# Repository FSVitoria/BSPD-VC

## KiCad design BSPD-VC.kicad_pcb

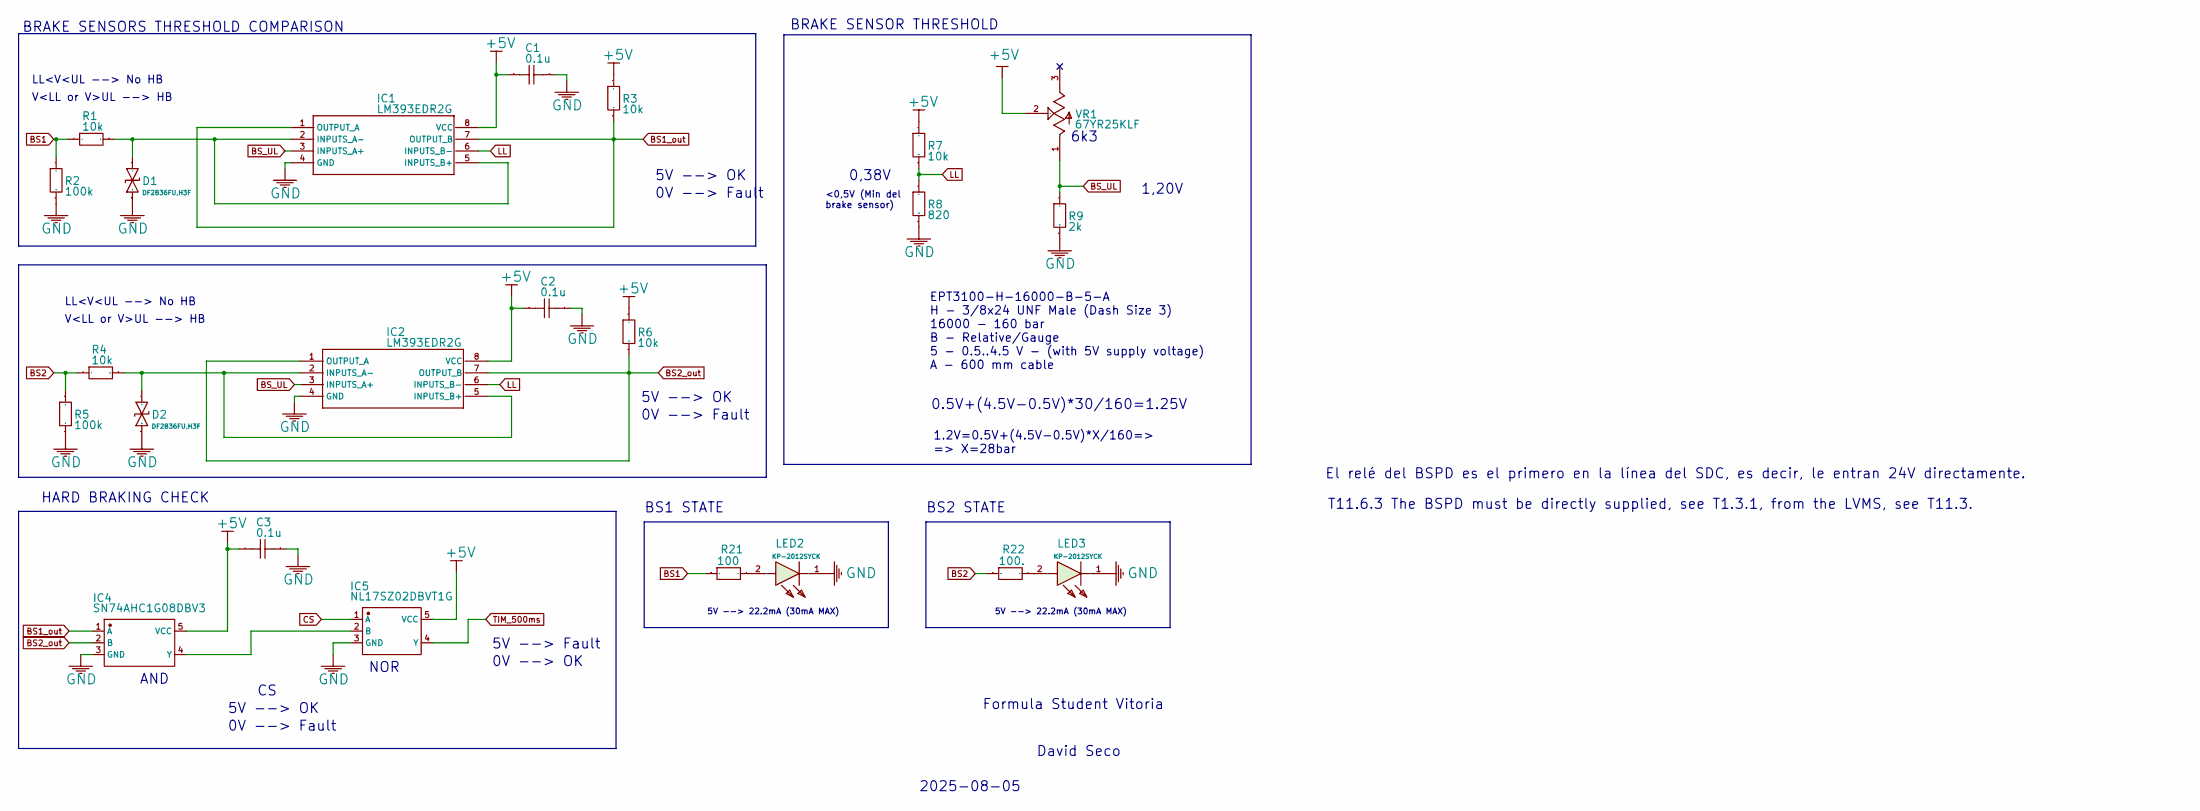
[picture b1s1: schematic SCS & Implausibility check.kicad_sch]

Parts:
C1, C2, C3: 0.1u; C0805
D1, D2: DF2B36FU,H3F; SOD-323_L1.7-W1.3-LS2.5-BI; Manufacturer Part DF2B36FU,H3F
IC1, IC2: LM393EDR2G; SOIC127P600X175-8N
IC4: SN74AHC1G08DBV3; SOT-23-5_L2.9-W1.6-P0.95-LS2.8-BR; Manufacturer Part SN74AHC1G08DBV3
IC5: NL17SZ02DBVT1G; SC-74A-5_L2.9-W1.6-P0.95-LS2.8-BR; Manufacturer Part NL17SZ02DBVT1G
LED2, LED3: KP-2012SYCK; LED_APHCM2012SURCK-F01
R1, R3, R4, R6, R7: 10k; R0805_NEW
R2, R5: 100k; R0805_NEW
R8: 820; R0805_NEW
R9: 2k; R0805_NEW
R21: 100; R0805
R22: 100.; R0805
VR1: 67YR25KLF; TRIM_67YR25KLFTB

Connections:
+5V: C1.1, C2.1, C3.2, IC1.8 (VCC), IC2.8 (VCC), IC4.5 (VCC), IC5.5 (VCC), R3.2, R6.2, R7.2, VR1.2; also elsewhere on the board
BS1: R1.2, R2.2, R21.1; also elsewhere on the board
BS1_out: IC1.1 (OUTPUT_A), IC1.7 (OUTPUT_B), IC4.1 (A), R3.1
BS2: R4.2, R5.2, R22.1; also elsewhere on the board
BS2_out: IC2.1 (OUTPUT_A), IC2.7 (OUTPUT_B), IC4.2 (B), R6.1
BS_UL: IC1.3 (INPUTS_A+), IC2.3 (INPUTS_A+), R9.2, VR1.1
CS: IC5.1 (A); also elsewhere on the board
GND: C1.2, C2.2, C3.1, D1.1, D2.1, IC1.4 (GND), IC2.4 (GND), IC4.3 (GND), IC5.3 (GND), LED2.1 (K), LED3.1 (K), R2.1, R5.1, R8.1, R9.1; also elsewhere on the board
LL: IC1.6 (INPUTS_B-), IC2.6 (INPUTS_B-), R7.1, R8.2
unnamed: D1.2, IC1.2 (INPUTS_A-), IC1.5 (INPUTS_B+), R1.1
unnamed: D2.2, IC2.2 (INPUTS_A-), IC2.5 (INPUTS_B+), R4.1
unnamed: IC4.4 (Y), IC5.2 (B)
unnamed: LED2.2 (A), R21.2
unnamed: LED3.2 (A), R22.2
TIM_500ms: IC5.4 (Y); also elsewhere on the board

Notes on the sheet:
5V --> 22.2mA (30mA MAX)
0,38V
El relé del BSPD es el primero en la línea del SDC, es decir, le entran 24V directamente.
5V --> OK
1.2V=0.5V+(4.5V-0.5V)*X/160=> => X=28bar
LL<V<UL --> No HB
6k3
NOR
5V --> Fault
BS2 STATE
V<LL or V>UL --> HB
0V --> Fault
T11.6.3 The BSPD must be directly supplied, see T1.3.1, from the LVMS, see T11.3.
BS1 STATE
0V --> OK
0.5V+(4.5V-0.5V)*30/160=1.25V
EPT3100-H-16000-B-5-A H - 3/8x24 UNF Male (Dash Size 3) 16000 - 160 bar B - Relative/Gauge 5 - 0.5..4.5 V - (with 5V supply voltage) A - 600 mm cable
Formula Student Vitoria
David Seco
AND
<0,5V (Min del brake sensor)
BRAKE SENSOR THRESHOLD
2025-08-05
5V --> 22.2mA (30mA MAX)
1,20V
BRAKE SENSORS THRESHOLD COMPARISON
HARD BRAKING CHECK

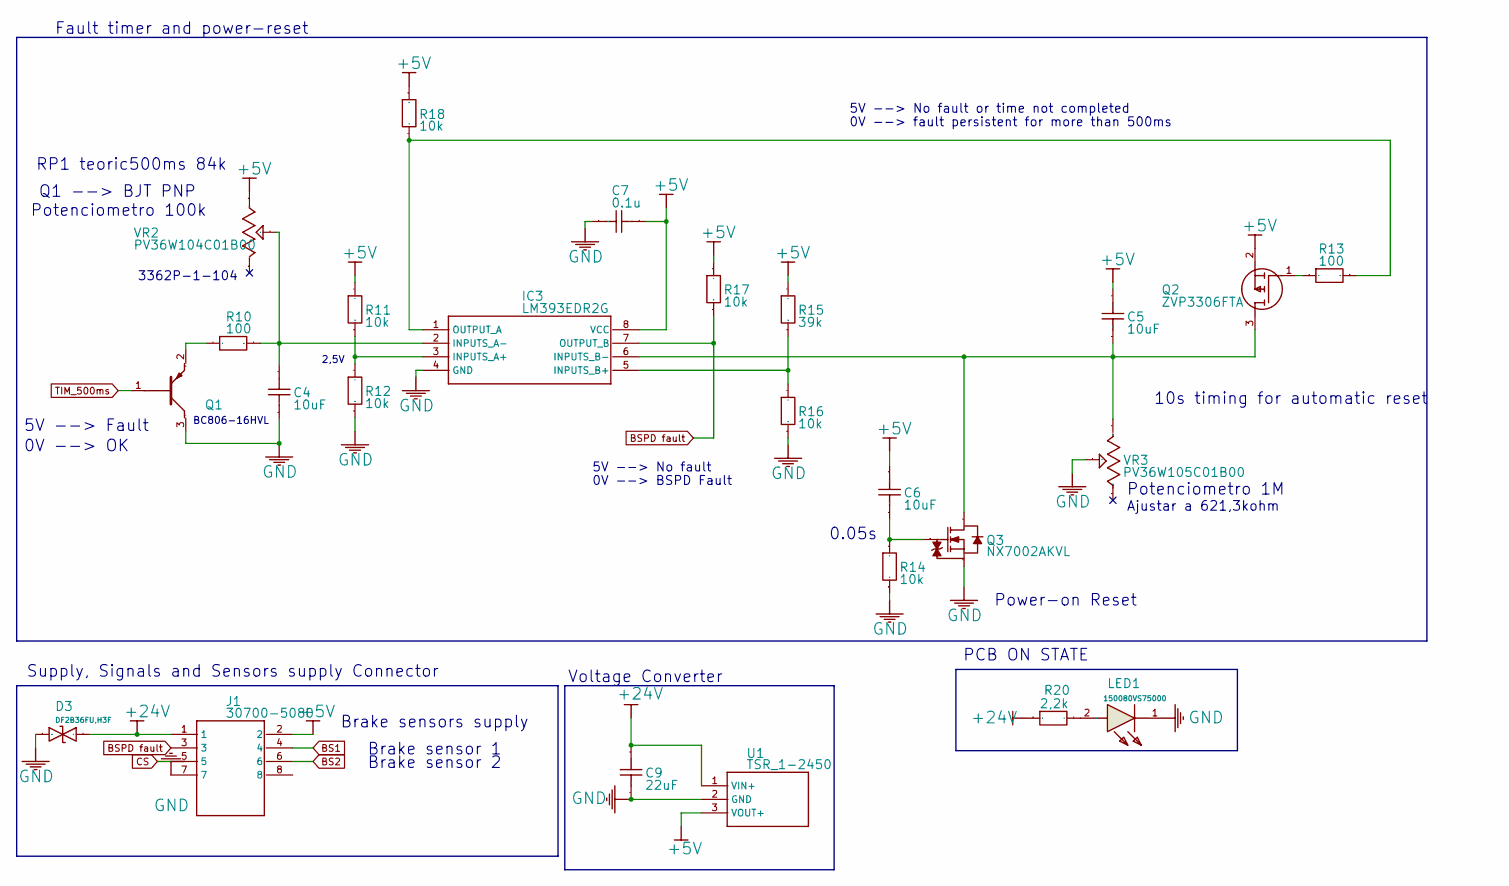
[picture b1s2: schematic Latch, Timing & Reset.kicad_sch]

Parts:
C4, C5, C6: 10uF; CAPAE430X610N
C7: 0.1u; C0805
C9: 22uF; C0805
D3: DF2B36FU,H3F; SOD-323_L1.7-W1.3-LS2.5-BI; Manufacturer Part DF2B36FU,H3F
IC3: LM393EDR2G; SOIC127P600X175-8N
J1: 30700-5080; 307005080
LED1: 150080VS75000; LEDC2012X80N
Q1: BC806-16HVL; SOT95P230X110-3N
Q2: ZVP3306FTA; SOT96P240X100-3N
Q3: NX7002AKVL; TO-236AB_L2.9-W1.3-P0.95-LS2.3-BR; Manufacturer Part NX7002AKVL
R10, R13: 100; R0805_NEW
R11, R12, R14, R16, R17, R18: 10k; R0805_NEW
R15: 39k; R0805_NEW
R20: 2,2k; R0805
U1: TSR_1-2450; TSR-1-24120
VR2: PV36W104C01B00; TRIM_PV36W104C01B00
VR3: PV36W105C01B00; TRIM_PV36W105C01B00

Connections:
+5V: C5.2, C6.2, C7.2, IC3.8 (VCC), J1.2, Q2.2 (S), R11.2, R15.2, R17.2, R18.1, U1.3 (VOUT+), VR2.1; also elsewhere on the board
+24V: C9.1, D3.2, J1.1, R20.1, U1.1 (VIN+)
BS1: J1.4; also elsewhere on the board
BS2: J1.6; also elsewhere on the board
BSPD fault: IC3.7 (OUTPUT_B), J1.3, R17.1
CS: J1.5; also elsewhere on the board
GND: C4.1, C7.1, C9.2, D3.1, IC3.4 (GND), J1.7, LED1.1 (K), Q1.3 (C), Q3.2 (S), R12.1, R14.1, R16.1, U1.2 (GND), VR3.2; also elsewhere on the board
unnamed: IC3.3 (INPUTS_A+), R11.1, R12.2
unnamed: C4.2, IC3.2 (INPUTS_A-), R10.1, VR2.2
unnamed: IC3.5 (INPUTS_B+), R15.1, R16.2
unnamed: C5.1, IC3.6 (INPUTS_B-), Q2.3 (D), Q3.3 (D), VR3.3
unnamed: IC3.1 (OUTPUT_A), R13.1, R18.2
unnamed: LED1.2 (A), R20.2
unnamed: Q1.2 (E), R10.2
unnamed: Q2.1 (G), R13.2
unnamed: C6.1, Q3.1 (G), R14.2
TIM_500ms: Q1.1 (B); also elsewhere on the board

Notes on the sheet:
2,5V
10s timing for automatic reset
Q1 --> BJT PNP
PCB ON STATE
5V --> Fault
5V --> No fault
Ajustar a 621,3kohm
5V --> No fault or time not completed
0V --> OK
RP1 teoric500ms 84k
BC806-16HVL
Brake sensor 2
Supply, Signals and Sensors supply Connector
Fault timer and power-reset
Voltage Converter
0V --> fault persistent for more than 500ms
0.05s
Brake sensor 1
Power-on Reset
Potenciometro 100k
3362P-1-104
Potenciometro 1M
0V --> BSPD Fault
Brake sensors supply

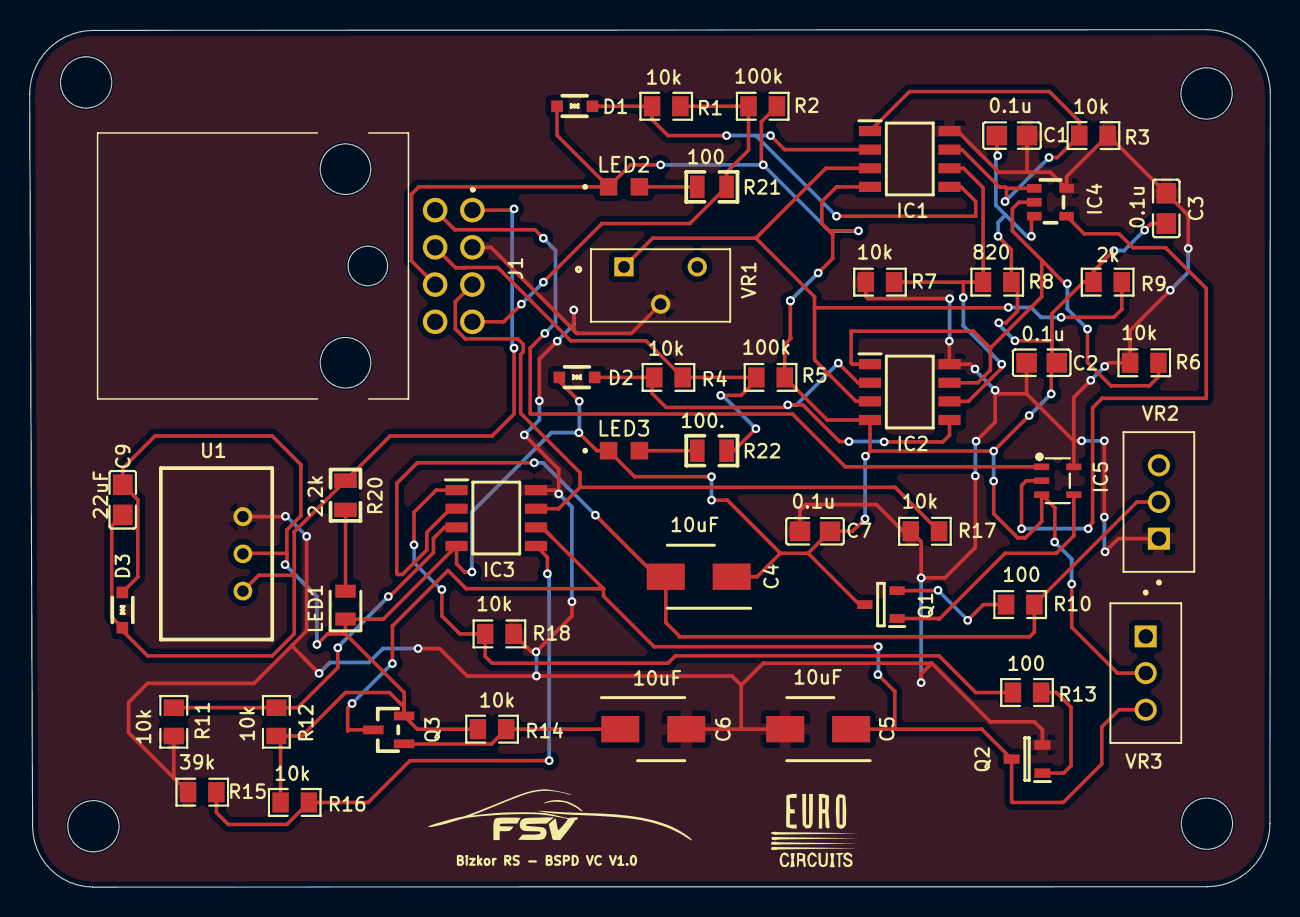
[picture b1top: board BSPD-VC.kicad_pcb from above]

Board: 2 copper layers, 84.6 x 58.5 mm, 48 parts (0 on the bottom side), 26 nets.
